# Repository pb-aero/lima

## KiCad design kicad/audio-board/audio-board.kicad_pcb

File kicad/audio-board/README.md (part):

# Audio board (AeroNode side) — clean-slate redo

**Status (measured 2026-11-09):** one A1 sheet, 120 parts (116 + 4 mounting holes), 140 nets, drawn entirely through Konnect.
Netlist matches `doc/design_nets.py` exactly; ERC 0 errors (4 expected strap warnings). All 120 parts have footprints.
The PCB is routed: 0 unconnected pads, 5 parity warnings on text fields only (Datasheet, Cable). **Schematic and layout
are not reviewed, and no board is recorded as built.** Published to the shelf as `reports/peter/LIMA_audio_board.html`.
Sheet notes corrected 2026-11-09, text only: netlist identical before and after. The sheet's title block is still
empty because Konnect has no tool for it; a text note above it identifies the sheet. Set it in Eeschema's Page Settings.
Started 2026-10-22, per Peter:
*"redo the audio board schematic on a clean slate using the new reference diagram from Juliette."*

**Reference:** JULIETT's interface spec, `Aerosense-Dev-Team-Sync:reports/john/2026-10-21_aeronode_audio_flow.pdf`
(company `1cf7160`, 10 pages), with John's 2026-10-21 rulings: the ADAU1467 hub is adopted
(`L-2026-W36-011`), the ADXL354 and ADAU1761 leave production, the cabin mic is single-ended analogue.

**What it replaces:** the ADAU1861 + AD2428 + ADXL354 + LTC6242 + level-shifter board last committed at
`72278d1` (`audio-board.kicad_sch` + `boom-mic-tx-select.kicad_sch`). That board was a different
architecture, not an earlier revision of this one; it stays retrievable from git at that SHA.

## Architecture (from the spec, §1–§2)

- **Normal — entirely digital.** Panel earphone → SP-74 (T2/T3) → high-Z tap → `ADAU1372 ADC1` → ADAU1467
  hub → (a) CM5 for AeroVault, (b) AD2428 → A2B → cups. Pilot voice: cup PDM mic → A2B → hub → CM5
  PureVoice → hub → `ADAU1372 DAC0` → buffer → K1 → panel mic line.
- **Bypass — entirely analogue, entirely aircraft-powered.** Panel audio → SP-74 → cup K2 N.C. → driver.
  Failsafe electret (console-biased) → K1 de-energised → panel mic line.
- **Cabin mic:** IM68A130A, single-ended analogue → `ADAU1372 ADC0`. No I²S mic.
- **Clock:** one 12.288 MHz XO → ADAU1467 `XTALIN/MCLK`; hub distributes `CLKOUT` and BCLK/LRCLK to the
  1372, CM5 (slave) and AD2428. Hub self-boots from EEPROM.
- **ICM-45686** (DVNC reference) is on SPI to the CM5 and never enters the audio chain — not on this board.

## Rulings (Peter, 2026-10-22)

| # | Ruling | Note |
|---|---|---|
| 1 | **Keep A2B**, per the spec | Peter floated I²S + power + bypass over an HDMI-type cable with JST ends, then withdrew it |
| 2 | **K1 = Panasonic AQW612S pair**, same as cup K2 | One package per leg; Form B (LED off) = electret → panel mic = bypass; Form A (LED on) = DAC → panel mic. Both legs broken, so our ground leaves the electret loop. Replaces the spec's "relay" and my earlier G6K-2 suggestion. At mic-level impedances (~1 kΩ) the 2.5 Ω on-resistance is negligible, so K2's open THD question barely applies here `[derived]` |
| 3 | ~~K1 LEDs driven from a TPS3430 watchdog kicked by the PureVoice process~~ | Ruled earlier the same day, then **superseded by 4** once the bare TPS3430 turned out not to latch (below) |
| 4 | **Watchdog left off for now** | K1 LEDs driven from a CM5 GPIO through a transistor, LEDs **off** at GPIO reset/high-Z (pull-down on the base), so power loss and CM5 boot both sit in bypass. `[default]` — the GPIO drive is my choice, not Peter's words. **Accepted residual:** power present + CM5 hung leaves K1 in NORMAL with a silent DAC on the panel mic — the spec §3 failure mode. Leave footprint room for a TPS3430 + 74LVC1G74 so it can return without a re-spin |
| 5 | ~~A2B part is the AD2428, not the AD2433~~ — **superseded by 6 the same day** — both ends (AeroNode main node, each cup sub-node) | Peter, 2026-10-22, after the AD2433's full data sheet turned out to be NDA-only. **Reverses the 2026-09-25 choice** (JULIETT `2026-09-25-003`), whose reason was that the AD2428W has **no SPI**, so DVNC/ANC coefficients cannot go *CM5 → SPI → A2B → cup ADAU1861* as spec §2 draws. They go by **A2B remote I²C** instead. `docs/a2b-remote-i2c-throughput.md` (2026-09-25) found that viable: 14 kB/s against a 384 kB/s control-header ceiling `[derived]`. **Condition carried with it:** erratum 18000075 — a failed remote-I²C write may not report an error, so coefficients must be written with **read-back verification**, or the canceller silently stops tracking; erratum 18000052 — remote I²C contends with GPIO-over-distance for the same header fields. **John/JULIETT not yet told** |
| 6 | ~~A2B part is the AD2433 at both ends~~ — **superseded by 9** — AeroNode main node and each cup sub-node | Peter, 2026-10-22, once the SPI point was clear. Restores JULIETT `2026-09-25-003`: coefficients go *CM5 → SPI0 → hub → AD2433 SPI over distance → cup ADAU1861*, landing straight in DSP memory. Ruling 5's remote-I²C errata no longer apply to the coefficient path. **Brings back the NDA blocker** for the AD2433 symbol (below) |
| 7 | **I²S from the CM5 to the audio board** | Peter, 2026-10-22. CM5 is I²S slave to the hub (spec §4). Over the AeroNode's existing audio header J3/J4 — below |
| 8 | **DVNC/ANC coefficients travel as audio data, not SPI** — CM5 → spare I²S lane → hub → A2B downstream TDM slot → cup ADAU1861 serial port → unpacked by the cup DSP | Peter, 2026-10-22, because the AeroNode audio header carries no SPI (option 1 of the three below). **Lane:** `I2S1_SDO1` (J3.7) `[default]`. **Requirements this creates:** (a) the hub must route that channel **bit-exact** — no gain, mix, ASRC, dither or limiter on it; (b) the stream carries its own **framing + CRC**, and the cup **keeps its previous coefficients** when a block fails — an audio slot has no ACK; (c) **cup firmware** work on the HiFi 3z, the cost JULIETT's SPI route avoided; (d) **one more downstream slot** in the A2B TDM map (still unfrozen). Bandwidth: 1 slot × 32 bit × 48 kHz = 1.536 Mbit/s vs ~112 kbit/s needed `[derived]`. **Consequence:** the AD2433's only stated advantage over the AD2428 was SPI-over-A2B for exactly this path (JULIETT `2026-09-25-003`), so ruling 6's reason no longer holds — the AD2428 (non-NDA, symbol already in the library) would serve. **Ruled in 9.** John/JULIETT not told |
| 9 | **A2B part is the AD2428 at both ends** — AeroNode main node and each cup sub-node | Peter, 2026-10-22, once ruling 8 took SPI out of the coefficient path: full data sheet public (`docs/datasheets/AD242x_RevC.pdf`), symbol already in `AnalogDevices`. Remote I²C over A2B is now **control traffic only**, so errata 18000075/18000052 touch configuration, not the canceller. **Slot capacity `[fetched]`** AD242x TRM: *"Up to 32 channels (1 x TDM32 or 2 x TDM16)"*, TDM2–TDM32 per pin — the two-slot cap asked about in JULIETT `2026-09-25-003` §2.3 is the PDM-clocked-from-BCLK case only (TDM2/32 or TDM4/16), which does not apply: the cup voice mic is on the ADAU1861's DMIC, not the AD2428's PDM pins |
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
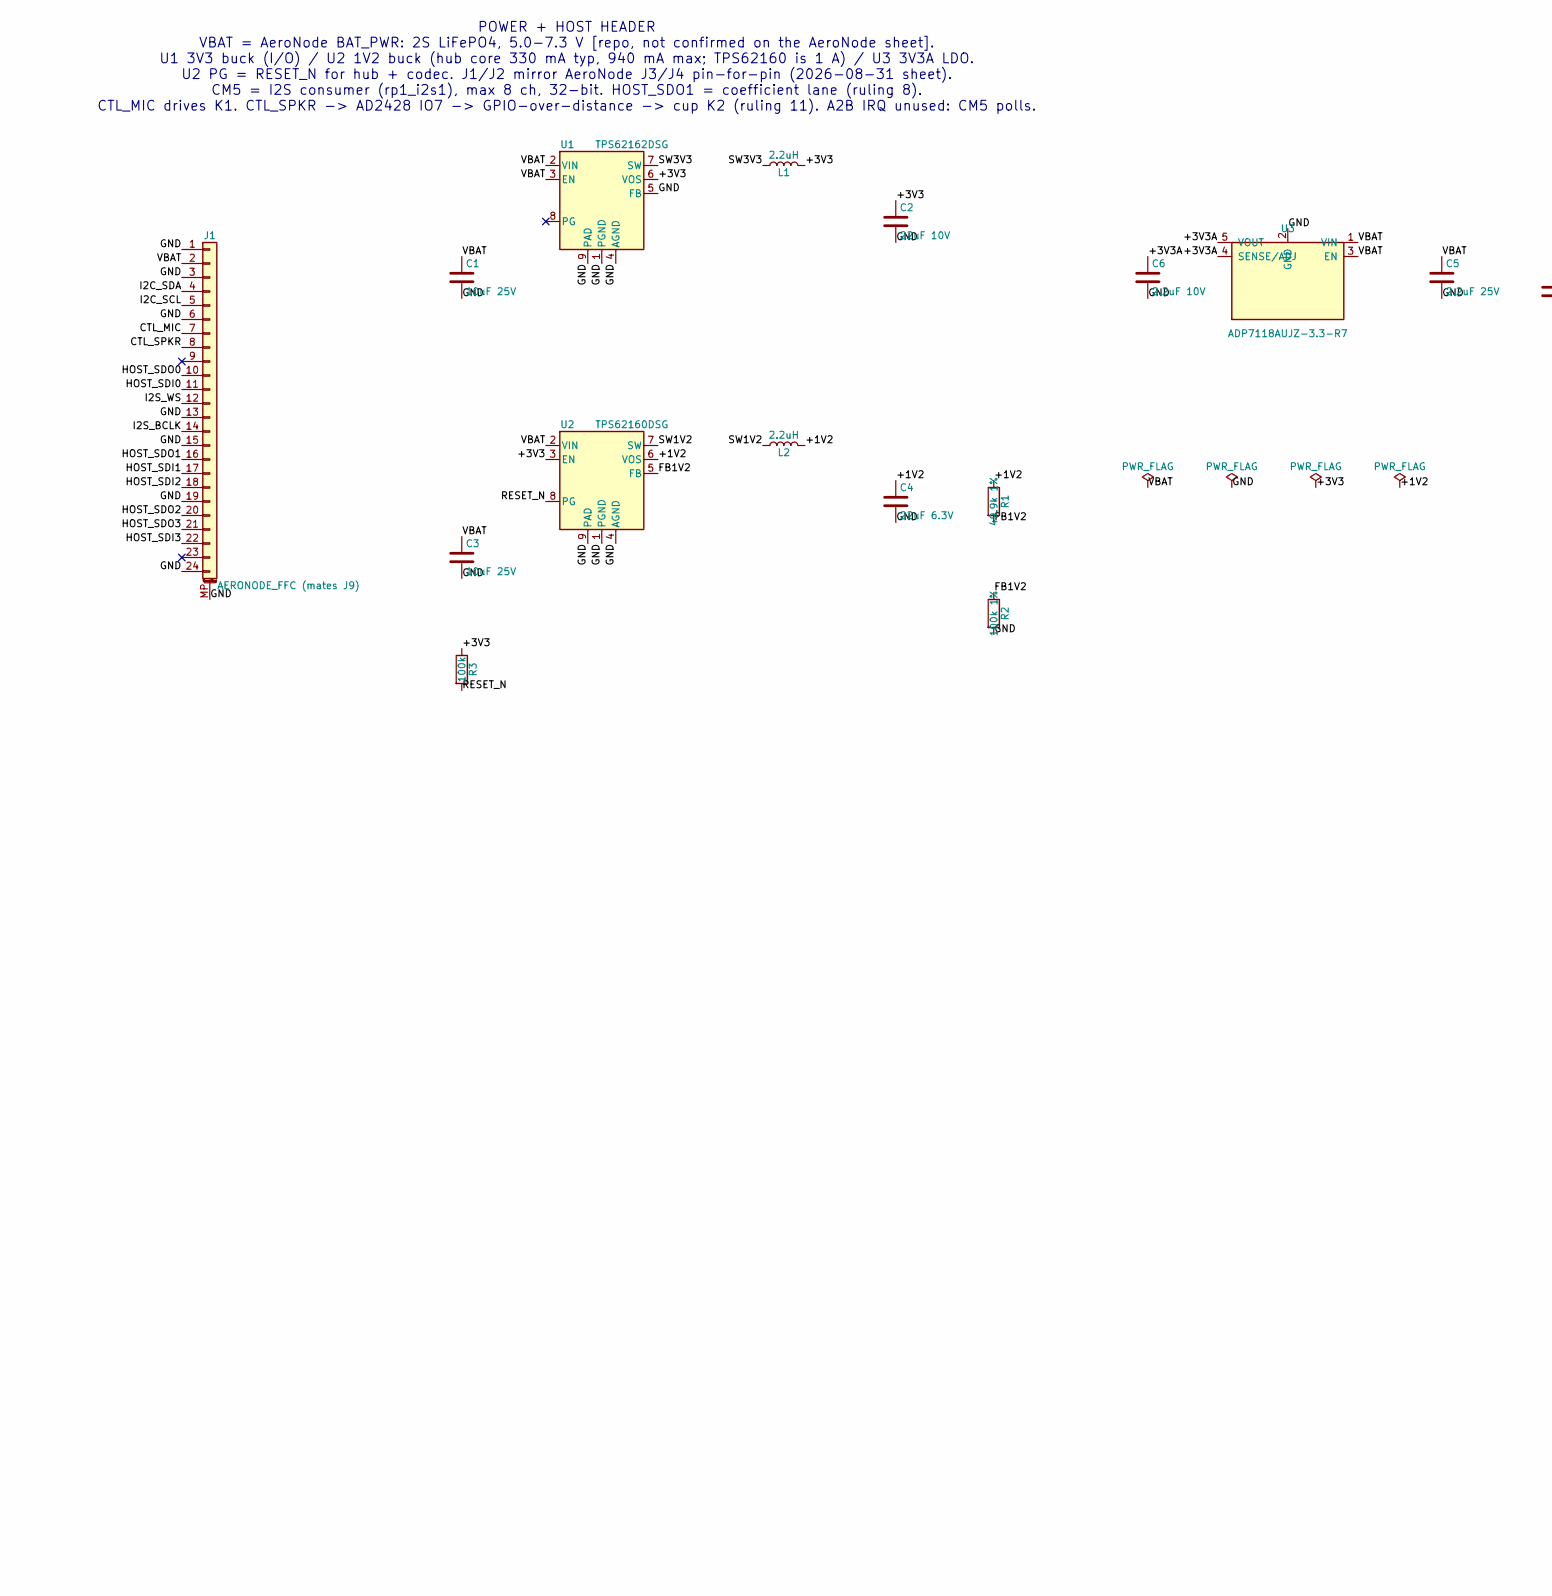
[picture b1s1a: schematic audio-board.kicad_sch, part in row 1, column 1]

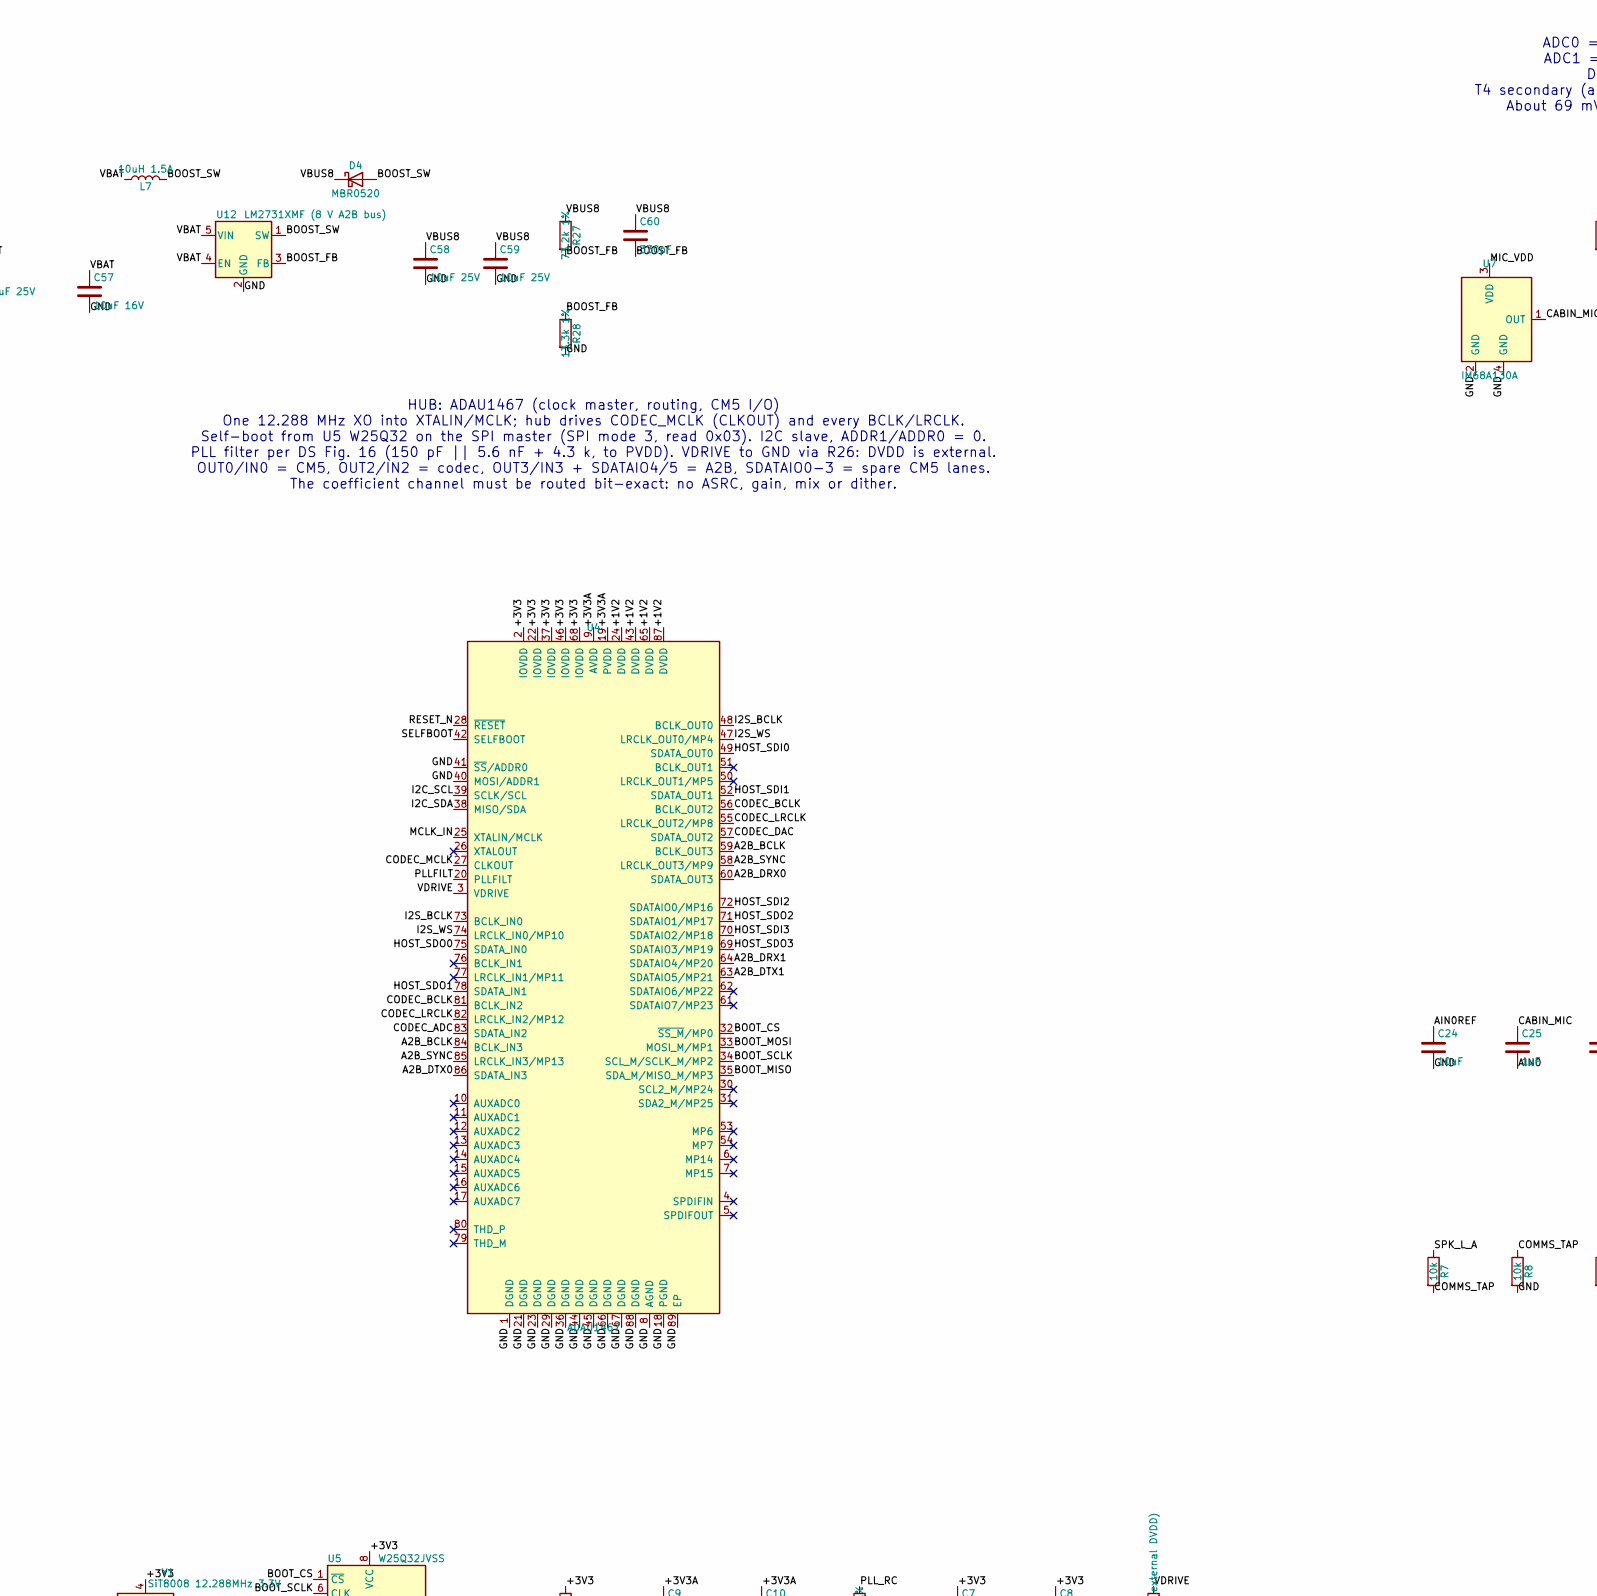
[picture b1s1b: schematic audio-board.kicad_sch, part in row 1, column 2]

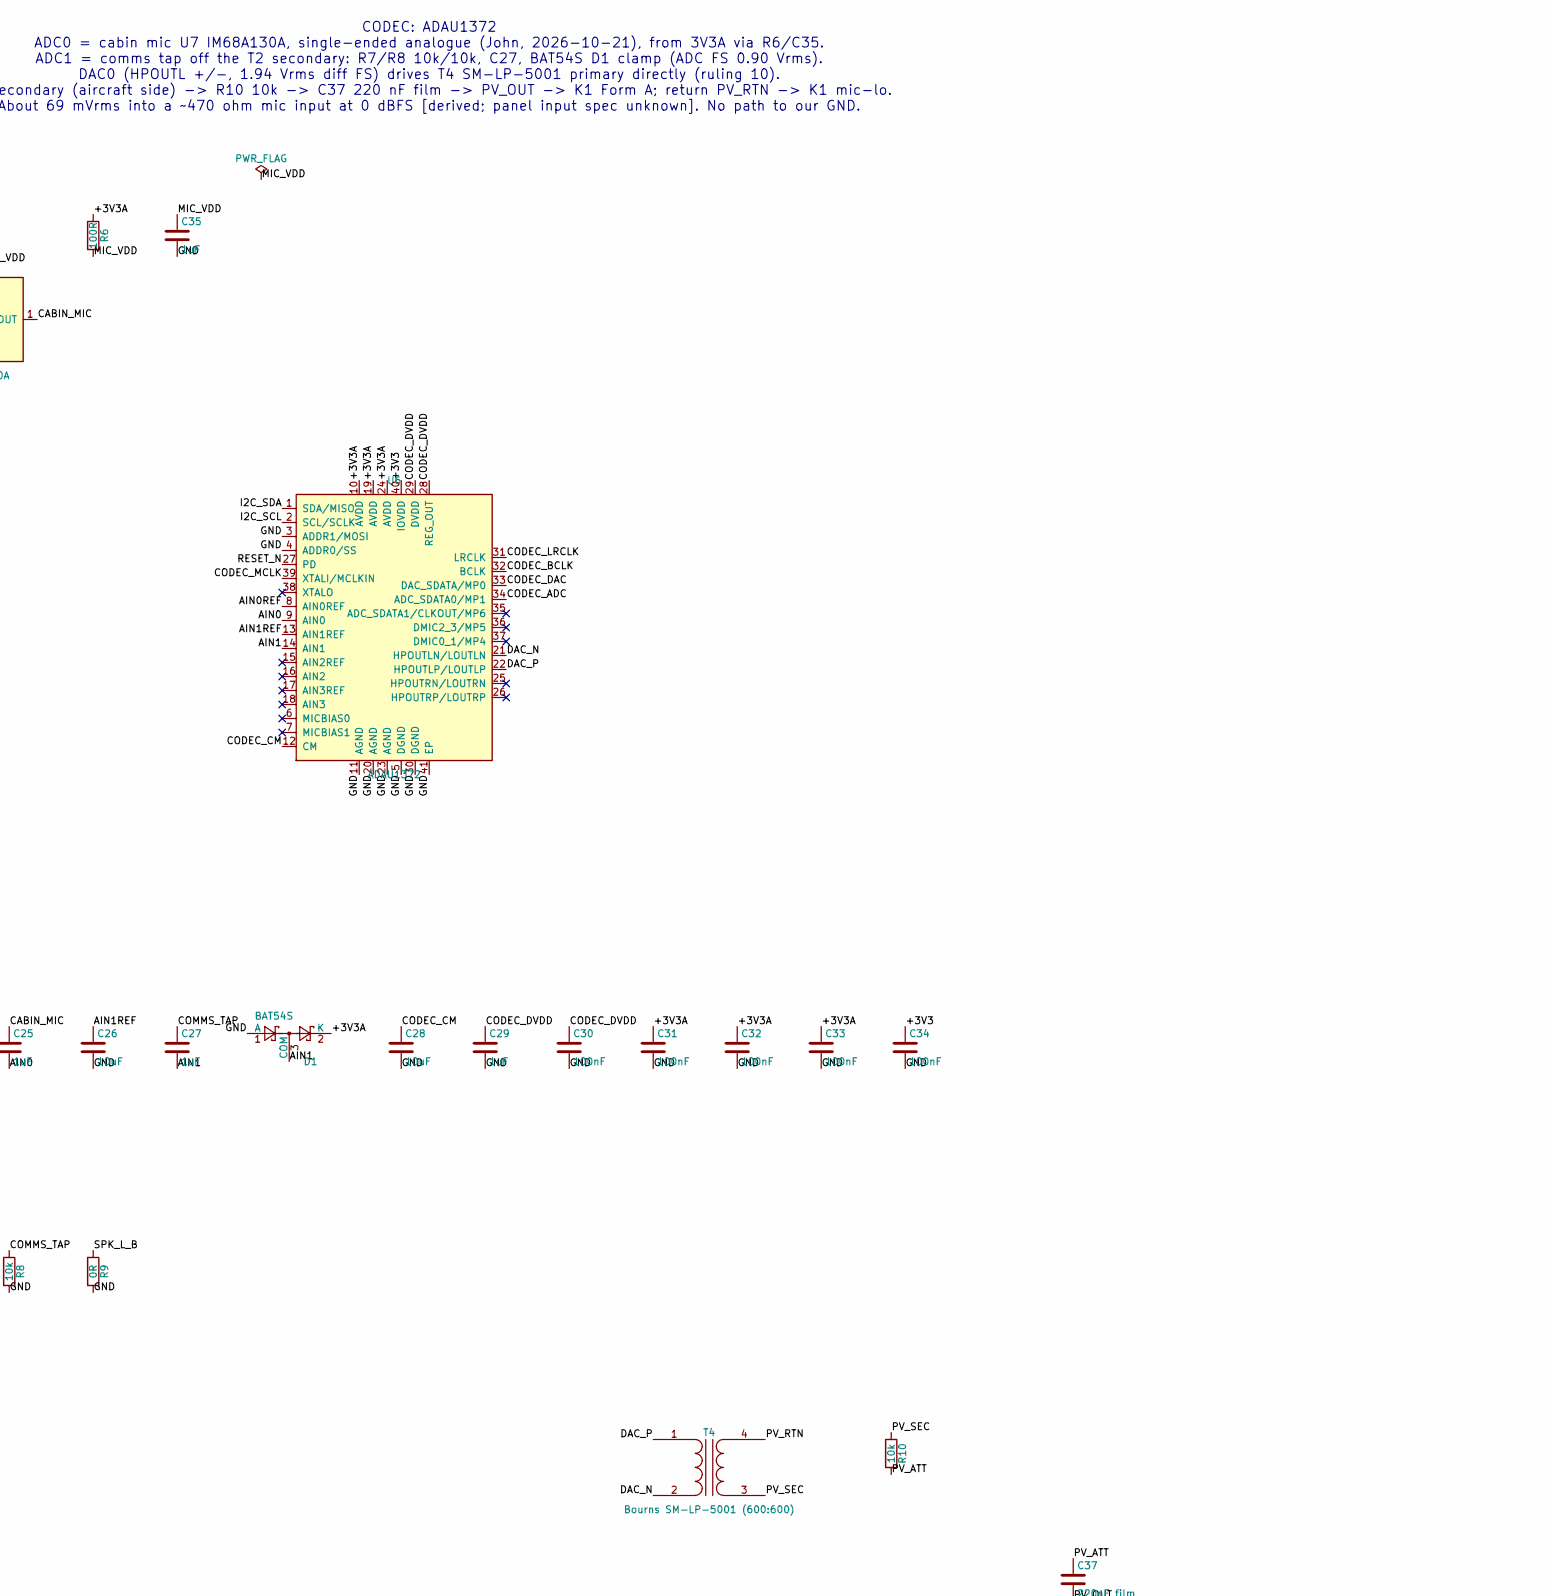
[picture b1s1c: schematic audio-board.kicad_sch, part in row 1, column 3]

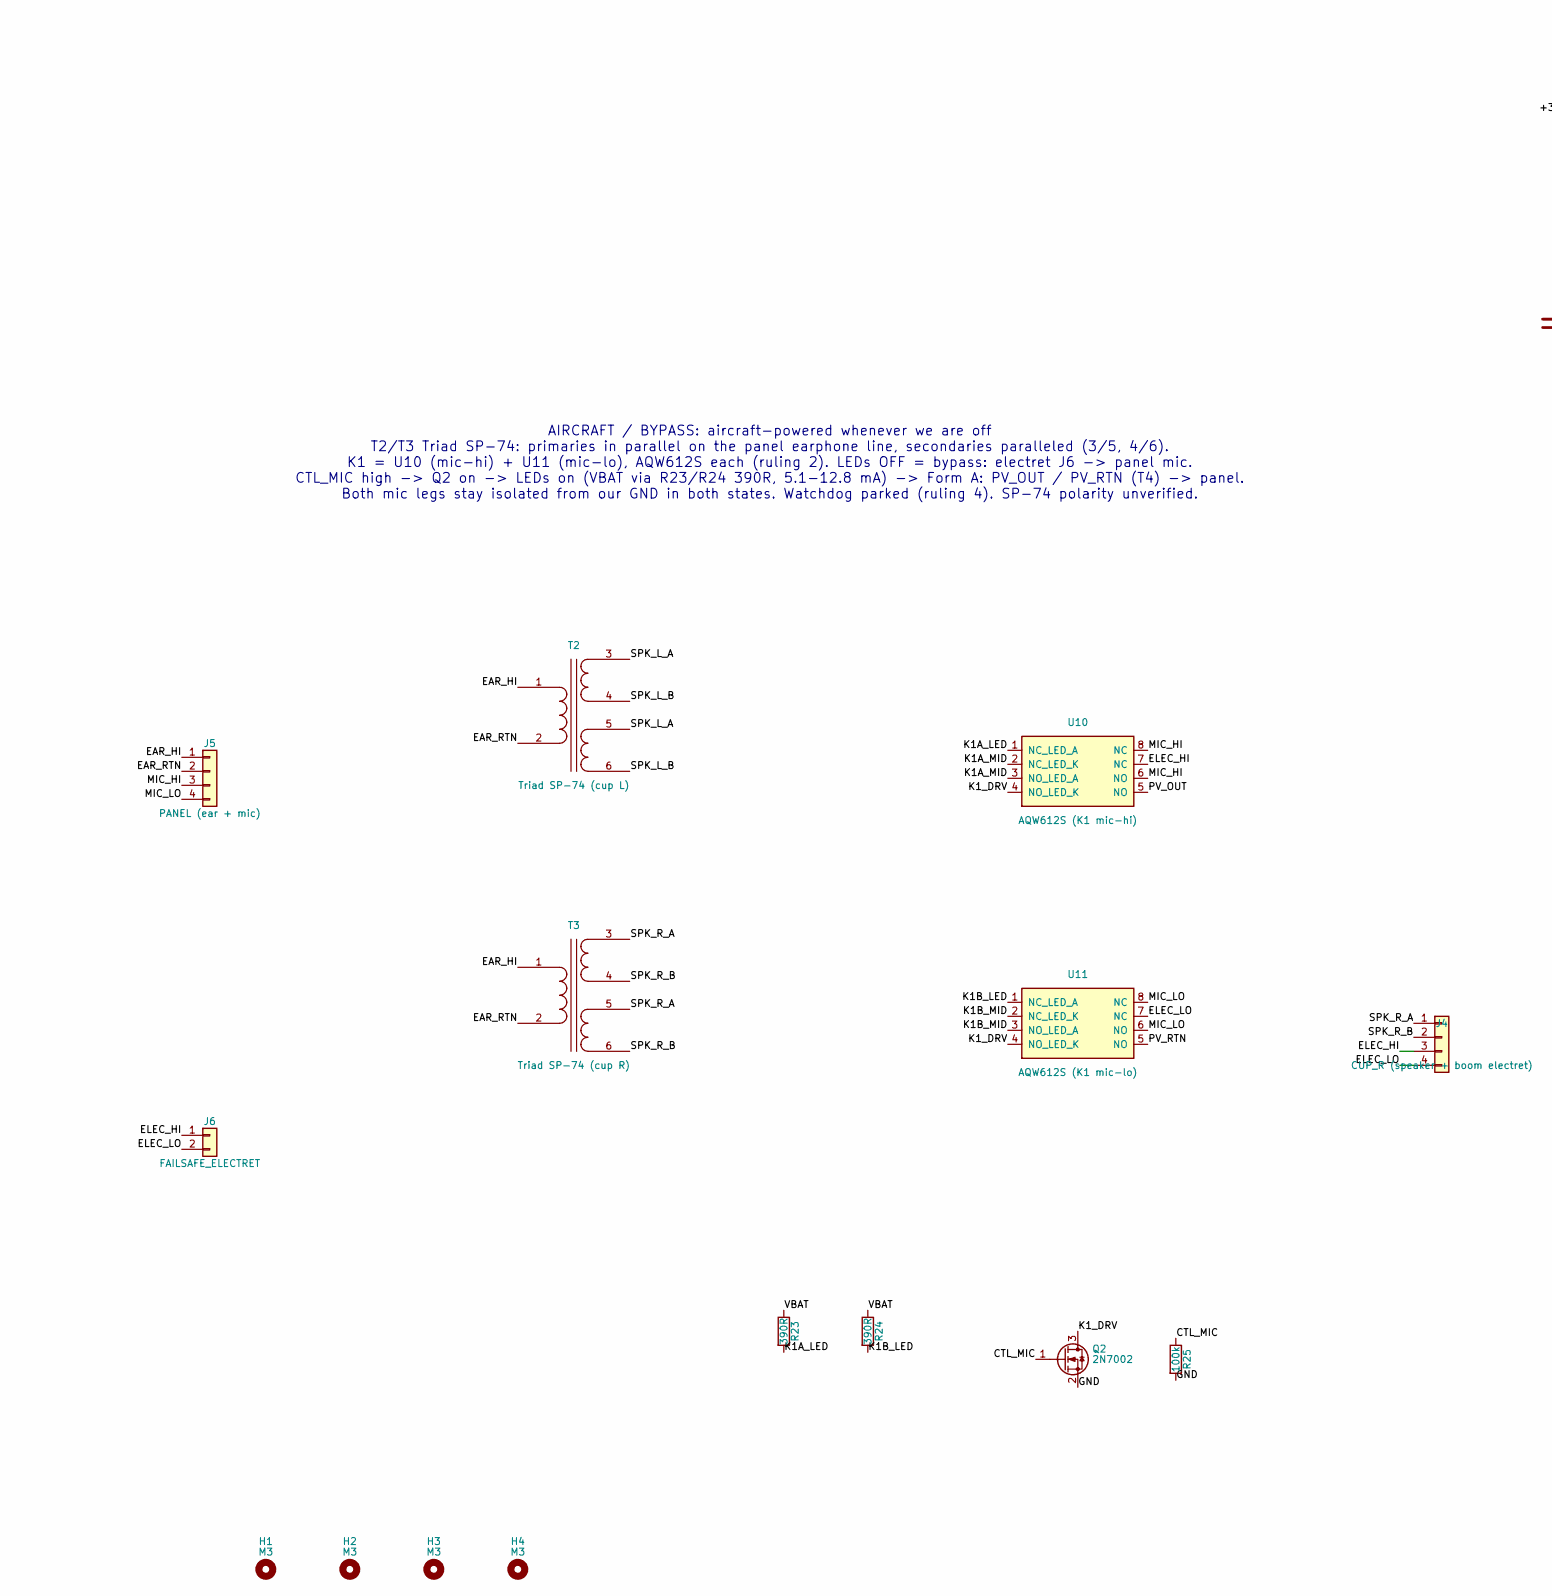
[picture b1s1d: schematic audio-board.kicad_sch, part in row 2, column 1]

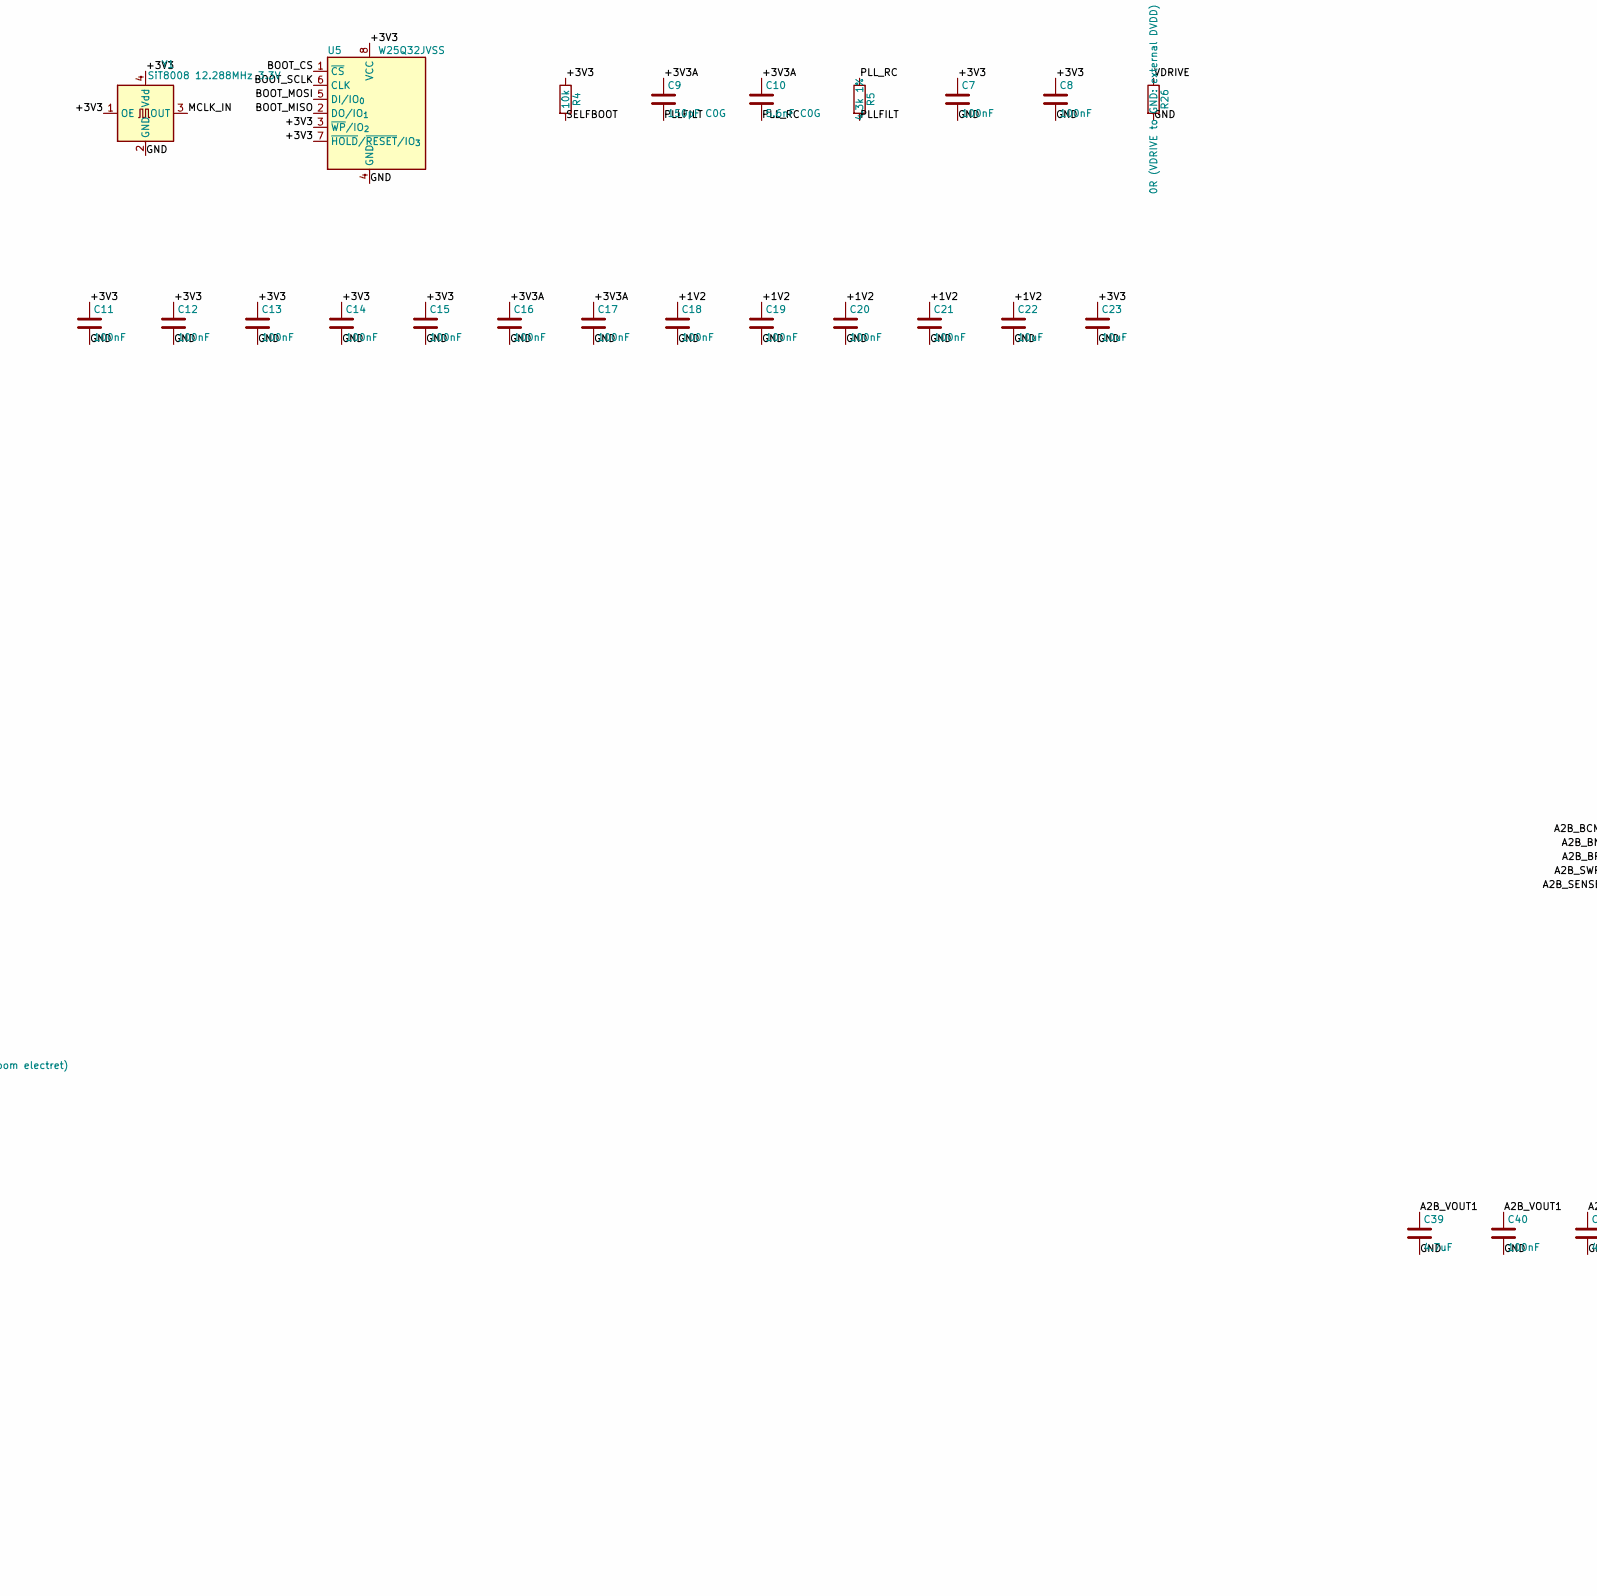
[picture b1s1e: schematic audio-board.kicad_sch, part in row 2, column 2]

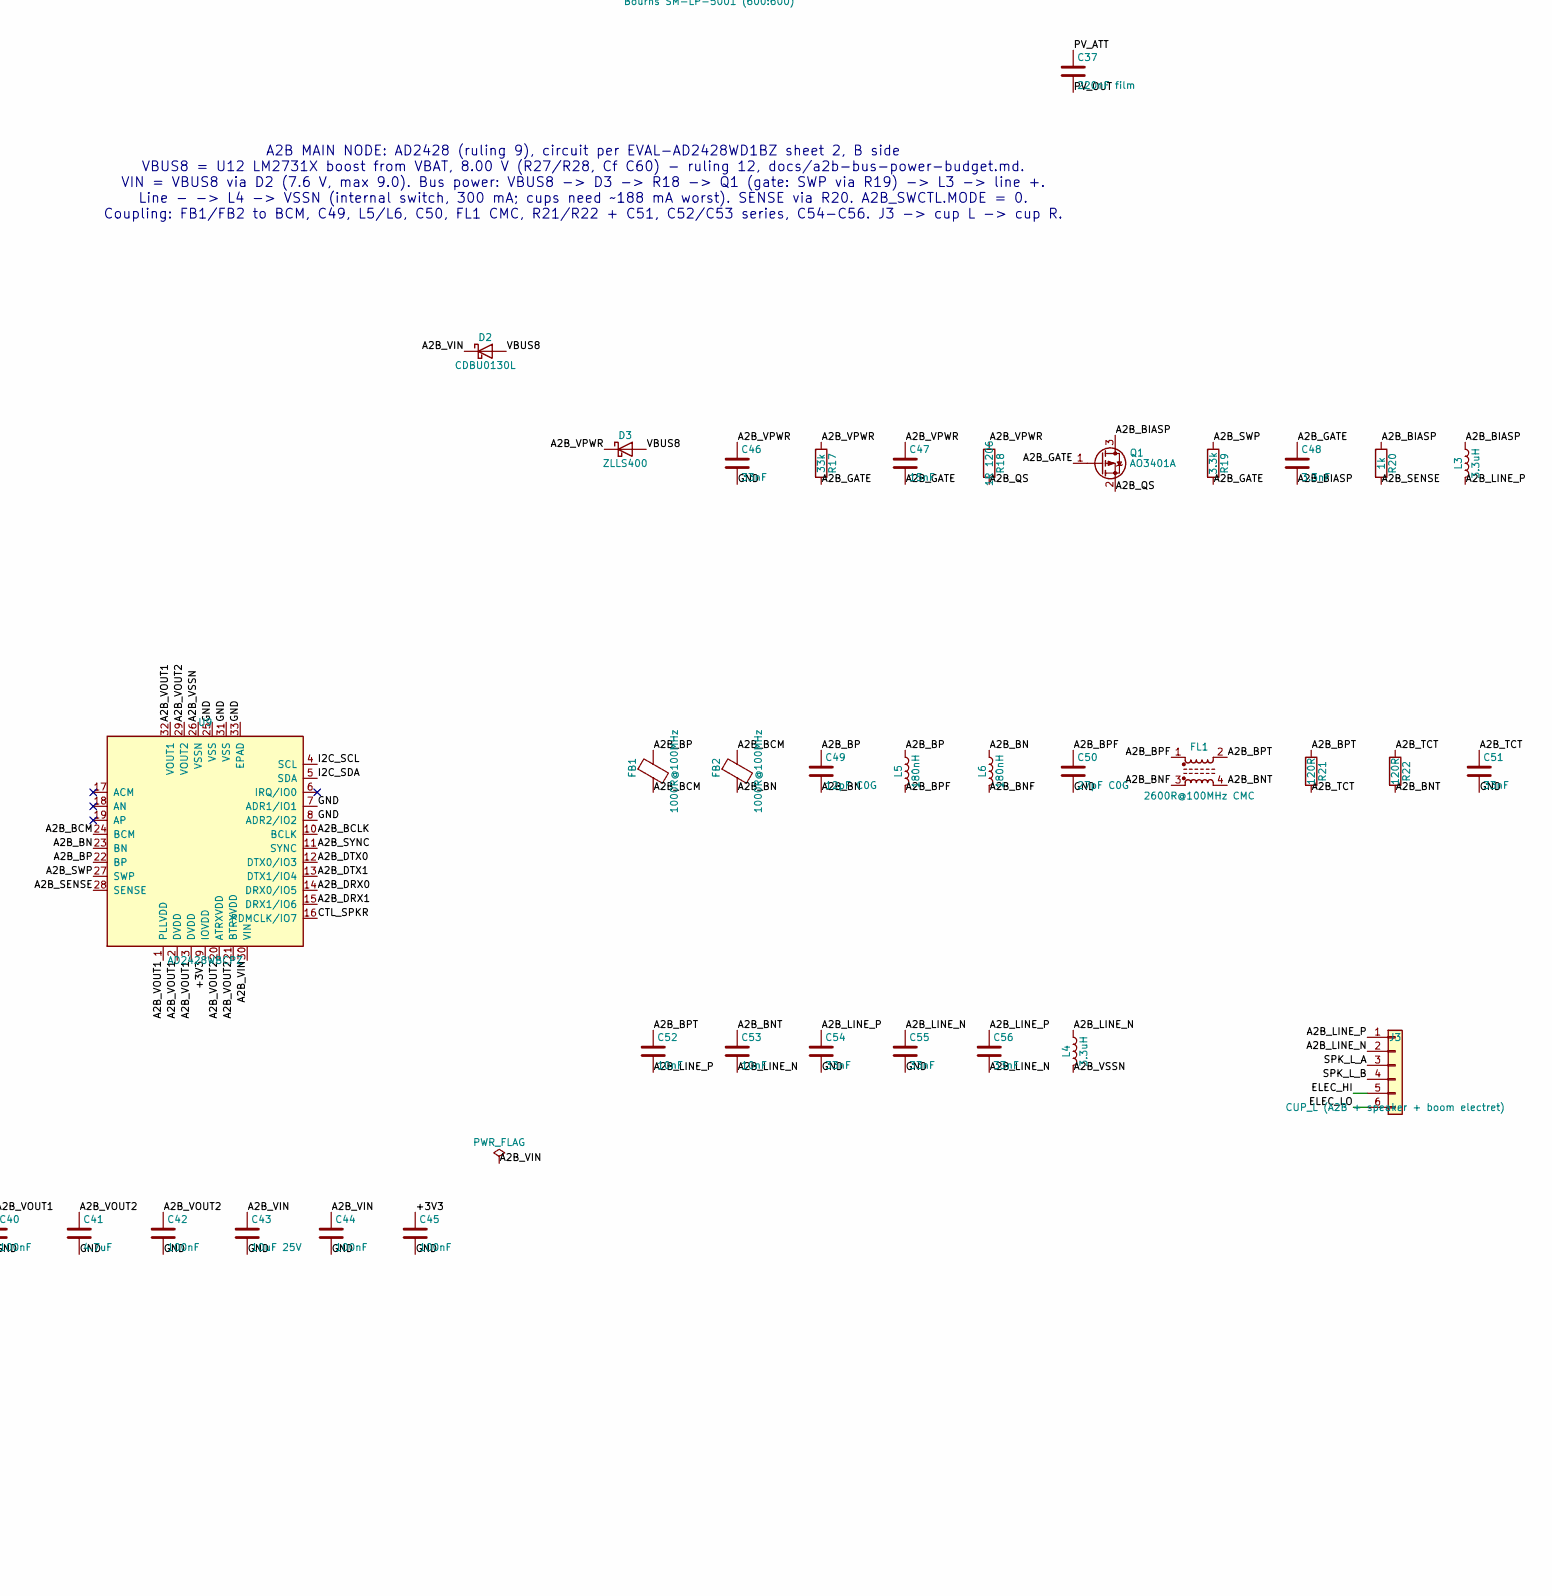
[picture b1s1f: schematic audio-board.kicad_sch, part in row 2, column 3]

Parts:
C1, C3, C43, C58, C59: 10uF 25V; C_0805_2012Metric
C2: 22uF 10V; C_0805_2012Metric
C4: 22uF 6.3V; C_0805_2012Metric
C5: 2.2uF 25V; C_0603_1608Metric
C6: 2.2uF 10V; C_0603_1608Metric
C7, C8, C11, C12, C13, C14, C15, C16, C17, C18, C19, C20, C21, C30, C31, C32, C33, C34, C40, C42, C44, C45: 100nF; C_0603_1608Metric
C9: 150pF C0G; C_0603_1608Metric
C10: 5.6nF C0G; C_0603_1608Metric
C22, C23, C24, C26, C28: 10uF; C_0805_2012Metric
C25, C27, C29, C35: 1uF; C_0603_1608Metric
C37: 220nF film; C_1812_4532Metric
C39, C41: 4.7uF; C_0603_1608Metric
C46, C51, C54, C55, C56: 33nF; C_0603_1608Metric
C47: 15nF; C_0603_1608Metric
C48: 3.3nF; C_0603_1608Metric
C49: 12pF C0G; C_0603_1608Metric
C50: 27pF C0G; C_0603_1608Metric
C52, C53: 10nF; C_0603_1608Metric
C57: 10uF 16V; C_0805_2012Metric
C60: 330pF; C_0603_1608Metric
D1: BAT54S; SOT-23
D2: CDBU0130L; D_0603_1608Metric
D3: ZLLS400; D_SOD-323
D4: MBR0520; D_SOD-123
FB1, FB2: 1000R@100MHz; L_0603_1608Metric
FL1: 2600R@100MHz CMC; L_CommonModeChoke_Coilank_ACM3216
H1, H2, H3, H4: M3; MountingHole_3.2mm_M3
J1: AERONODE_FFC (mates J9); Cvilux_CF31241D0R0-05-NH_1x24-1MP_P0.5mm_Horizontal; MPN Cvilux CF31241D0R0-05-NH
J3: CUP_L (A2B + speaker + boom electret); JST_GH_SM06B-GHS-TB_1x06-1MP_P1.25mm_Horizontal
J4: CUP_R (speaker + boom electret); JST_GH_SM04B-GHS-TB_1x04-1MP_P1.25mm_Horizontal
J5: PANEL (ear + mic); JST_GH_SM04B-GHS-TB_1x04-1MP_P1.25mm_Horizontal
J6: FAILSAFE_ELECTRET; JST_GH_SM02B-GHS-TB_1x02-1MP_P1.25mm_Horizontal
L1, L2: 2.2uH; L_1008_2520Metric
L3, L4: 3.3uH; L_1210_3225Metric
L5, L6: 180nH; L_0603_1608Metric
L7: 10uH 1.5A; L_Coilcraft_XAL4030-XXX
Q1: AO3401A; SOT-23
Q2: 2N7002; SOT-23
R1: 49.9k 1%; R_0603_1608Metric
R2: 100k 1%; R_0603_1608Metric
R3, R25: 100k; R_0603_1608Metric
R4, R7, R8, R10: 10k; R_0603_1608Metric
R5: 4.3k 1%; R_0603_1608Metric
R6: 100R; R_0603_1608Metric
R9: 0R; R_0603_1608Metric
R17: 33k; R_0603_1608Metric
R18: 1R 1206; R_1206_3216Metric
R19: 3.3k; R_0603_1608Metric
R20: 1k; R_0603_1608Metric
R21, R22: 120R; R_0603_1608Metric
R23, R24: 390R; R_0603_1608Metric
R26: 0R (VDRIVE to GND: external DVDD); R_0603_1608Metric
R27: 73.2k 1%; R_0603_1608Metric
R28: 13.3k 1%; R_0603_1608Metric
T2: Triad SP-74 (cup L); Triad_SP-74_THT_10.4x7.9mm_P2.54mm
T3: Triad SP-74 (cup R); Triad_SP-74_THT_10.4x7.9mm_P2.54mm
T4: Bourns SM-LP-5001 (600:600); Bourns_SM-LP-5001_12.8x9.0mm_P2.54mm
U1: TPS62162DSG; WSON-8-1EP_2x2mm_P0.5mm_EP0.9x1.6mm_ThermalVias
U2: TPS62160DSG; WSON-8-1EP_2x2mm_P0.5mm_EP0.9x1.6mm_ThermalVias
U3: ADP7118AUJZ-3.3-R7; TSOT-23-5
U4: ADAU1467; AD_LFCSP-88-1EP_12x12mm_P0.5mm_EP5.3x5.3mm_CP-88-10
U5: W25Q32JVSS; SOIC-8_5.3x5.3mm_P1.27mm
U6: ADAU1372; AD_LFCSP-40-1EP_6x6mm_P0.5mm_EP4.3x4.3mm_CP-40-10
U7: IM68A130A; Infineon_PG-TLGA-4-2_3.35x2.5mm_IM68A130A
U9: AD2428WBCPZ; QFN-32-1EP_5x5mm_P0.5mm_EP3.6x3.6mm_ThermalVias
U10: AQW612S (K1 mic-hi); Panasonic_GU-SOP8_4.4x9.37mm_P2.54mm_AQW61xS
U11: AQW612S (K1 mic-lo); Panasonic_GU-SOP8_4.4x9.37mm_P2.54mm_AQW61xS
U12: LM2731XMF (8 V A2B bus); SOT-23-5
Y1: SiT8008 12.288MHz 3.3V; Oscillator_SMD_SiT_PQFN-4Pin_3.2x2.5mm

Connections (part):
/+1V2: C4.1, C18.1, C19.1, C20.1, C21.1, C22.1, L2.2, R1.1, U2.6 (VOS), U4.24 (DVDD), U4.43 (DVDD), U4.65 (DVDD), U4.87 (DVDD)
/+3V3: C2.1, C7.1, C8.1, C11.1, C12.1, C13.1, C14.1, C15.1, C23.1, C34.1, C45.1, L1.2, R3.1, R4.1, U1.6 (VOS), U2.3 (EN), U4.2 (IOVDD), U4.22 (IOVDD), U4.37 (IOVDD), U4.46 (IOVDD), U4.68 (IOVDD), U5.3 (~WP/IO_{2}), U5.7 (~HOLD/~RESET/IO_{3}), U5.8 (VCC), U6.40 (IOVDD), U9.9 (IOVDD), Y1.1 (OE), Y1.4 (Vdd)
/+3V3A: C6.1, C9.1, C10.1, C16.1, C17.1, C31.1, C32.1, C33.1, D1.2 (K), R6.1, U3.4 (SENSE/ADJ), U3.5 (VOUT), U4.9 (AVDD), U4.19 (PVDD), U6.10 (AVDD), U6.19 (AVDD), U6.24 (AVDD)
/A2B_BCLK: U4.59 (BCLK_OUT3), U4.84 (BCLK_IN3), U9.10 (BCLK)
/A2B_BCM: FB1.2, FB2.1, U9.24 (BCM)
/A2B_BIASP: C48.2, L3.1, Q1.3 (D), R20.1
/A2B_BN: C49.2, FB2.2, L6.1, U9.23 (BN)
/A2B_BNF: FL1.3, L6.2
/A2B_BNT: C53.1, FL1.4, R22.2
/A2B_BP: C49.1, FB1.1, L5.1, U9.22 (BP)
/A2B_BPF: C50.1, FL1.1, L5.2
/A2B_BPT: C52.1, FL1.2, R21.1
/A2B_DRX0: U4.60 (SDATA_OUT3), U9.14 (DRX0/IO5)
/A2B_DRX1: U4.64 (SDATAIO4/MP20), U9.15 (DRX1/IO6)
/A2B_DTX0: U4.86 (SDATA_IN3), U9.12 (DTX0/IO3)
/A2B_DTX1: U4.63 (SDATAIO5/MP21), U9.13 (DTX1/IO4)
/A2B_GATE: C47.2, C48.1, Q1.1 (G), R17.2, R19.2
/A2B_LINE_N: C53.2, C55.1, C56.2, J3.2, L4.1
/A2B_LINE_P: C52.2, C54.1, C56.1, J3.1, L3.2
/A2B_QS: Q1.2 (S), R18.2
/A2B_SENSE: R20.2, U9.28 (SENSE)
/A2B_SWP: R19.1, U9.27 (SWP)
/A2B_SYNC: U4.58 (LRCLK_OUT3/MP9), U4.85 (LRCLK_IN3/MP13), U9.11 (SYNC)
/A2B_TCT: C51.1, R21.2, R22.1
/A2B_VIN: C43.1, C44.1, D2.1 (K), U9.30 (VIN)
/A2B_VOUT1: C39.1, C40.1, U9.1 (PLLVDD), U9.2 (DVDD), U9.3 (DVDD), U9.32 (VOUT1)
/A2B_VOUT2: C41.1, C42.1, U9.20 (ATRXVDD), U9.21 (BTRXVDD), U9.29 (VOUT2)
/A2B_VPWR: C46.1, C47.1, D3.1 (K), R17.1, R18.1
/A2B_VSSN: L4.2, U9.26 (VSSN)
/AIN0: C25.2, U6.9 (AIN0)
/AIN0REF: C24.1, U6.8 (AIN0REF)
/AIN1: C27.2, D1.3 (COM), U6.14 (AIN1)
/AIN1REF: C26.1, U6.13 (AIN1REF)
/BOOST_FB: C60.2, R27.2, R28.1, U12.3 (FB)
/BOOST_SW: D4.2 (A), L7.2, U12.1 (SW)
/BOOT_CS: U4.32 (~SS_M/MP0), U5.1 (~CS)
/BOOT_MISO: U4.35 (SDA_M/MISO_M/MP3), U5.2 (DO/IO_{1})
/BOOT_MOSI: U4.33 (MOSI_M/MP1), U5.5 (DI/IO_{0})
/BOOT_SCLK: U4.34 (SCL_M/SCLK_M/MP2), U5.6 (CLK)
/CABIN_MIC: C25.1, U7.1 (OUT)
/CODEC_ADC: U4.83 (SDATA_IN2), U6.34 (ADC_SDATA0/MP1)
/CODEC_BCLK: U4.56 (BCLK_OUT2), U4.81 (BCLK_IN2), U6.32 (BCLK)
/CODEC_CM: C28.1, U6.12 (CM)
/CODEC_DAC: U4.57 (SDATA_OUT2), U6.33 (DAC_SDATA/MP0)
/CODEC_DVDD: C29.1, C30.1, U6.28 (REG_OUT), U6.29 (DVDD)
/CODEC_LRCLK: U4.55 (LRCLK_OUT2/MP8), U4.82 (LRCLK_IN2/MP12), U6.31 (LRCLK)
/CODEC_MCLK: U4.27 (CLKOUT), U6.39 (XTALI/MCLKIN)
/COMMS_TAP: C27.1, R7.2, R8.1
/CTL_MIC: J1.7, Q2.1 (G), R25.1
/CTL_SPKR: J1.8, U9.16 (PDMCLK/IO7)
/DAC_N: T4.2 (AB), U6.21 (HPOUTLN/LOUTLN)
/DAC_P: T4.1 (AA), U6.22 (HPOUTLP/LOUTLP)
/EAR_HI: J5.1, T2.1 (AA), T3.1 (AA)
/EAR_RTN: J5.2, T2.2 (AB), T3.2 (AB)
/ELEC_HI: J3.5, J4.3, J6.1, U10.7 (NC)
/ELEC_LO: J3.6, J4.4, J6.2, U11.7 (NC)
/FB1V2: R1.2, R2.1, U2.5 (FB)
/GND: C1.2, C2.2, C3.2, C4.2, C5.2, C6.2, C7.2, C8.2, C11.2, C12.2, C13.2, C14.2, C15.2, C16.2, C17.2, C18.2, C19.2, C20.2, C21.2, C22.2, C23.2, C24.2, C26.2, C28.2, C29.2, C30.2, C31.2, C32.2, C33.2, C34.2, C35.2, C39.2, C40.2, C41.2, C42.2, C43.2, C44.2, C45.2, C46.2, C50.2, C51.2, C54.2, C55.2, C57.2, C58.2, C59.2, D1.1 (A), J1.1, J1.3, J1.6, J1.13, J1.15, J1.19, J1.24, J1.MP (MountPin), Q2.2 (S), R2.2, R8.2, R9.2, R25.2, R26.2, R28.2, U1.1 (PGND), U1.4 (AGND), U1.5 (FB), U1.9 (PAD), U2.1 (PGND), U2.4 (AGND), U2.9 (PAD), U3.2 (GND), U4.1 (DGND), U4.8 (AGND), U4.18 (PGND), U4.21 (DGND), U4.23 (DGND), U4.29 (DGND), U4.36 (DGND), U4.40 (MOSI/ADDR1), U4.41 (~SS/ADDR0), U4.44 (DGND)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
/HOST_SDI0: J1.11, U4.49 (SDATA_OUT0)
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
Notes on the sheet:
HUB: ADAU1467 (clock master, routing, CM5 I/O) One 12.288 MHz XO into XTALIN/MCLK; hub drives CODEC_MCLK (CLKOUT) and every BCLK/LRCLK. Self-boot from U5 W25Q32 on the SPI master (SPI mode 3, read 0x03). I2C slave, ADDR1/ADDR0 = 0. PLL filter per DS Fig. 16 (150 pF || 5.6 nF + 4.3 k, to PVDD). VDRI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
CODEC: ADAU1372 ADC0 = cabin mic U7 IM68A130A, single-ended analogue (John, 2026-10-21), from 3V3A via R6/C35. ADC1 = comms tap off the T2 secondary: R7/R8 10k/10k, C27, BAT54S D1 clamp (ADC FS 0.90 Vrms). DAC0 (HPOUTL +/-, 1.94 Vrms diff FS) drives T4 SM-LP-5001 primary directly (ruling 10). T4 se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
AIRCRAFT / BYPASS: aircraft-powered whenever we are off T2/T3 Triad SP-74: primaries in parallel on the panel earphone line, secondaries paralleled (3/5, 4/6). K1 = U10 (mic-hi) + U11 (mic-lo), AQW612S each (ruling 2). LEDs OFF = bypass: electret J6 -> panel mic. CTL_MIC high -> Q2 on -> LEDs on (V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
POWER + HOST HEADER VBAT = AeroNode BAT_PWR: 2S LiFePO4, 5.0-7.3 V [repo, not confirmed on the AeroNode sheet]. U1 3V3 buck (I/O) / U2 1V2 buck (hub core 330 mA typ, 940 mA max; TPS62160 is 1 A) / U3 3V3A LDO. U2 PG = RESET_N for hub + codec. J1/J2 mirror AeroNode J3/J4 pin-for-pin (2026-08-31 shee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
A2B MAIN NODE: AD2428 (ruling 9), circuit per EVAL-AD2428WD1BZ sheet 2, B side VBUS8 = U12 LM2731X boost from VBAT, 8.00 V (R27/R28, Cf C60) - ruling 12, docs/a2b-bus-power-budget.md. VIN = VBUS8 via D2 (7.6 V, max 9.0). Bus power: VBUS8 -> D3 -> R18 -> Q1 (gate: SWP via R19) -> L3 -> line +. Line 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

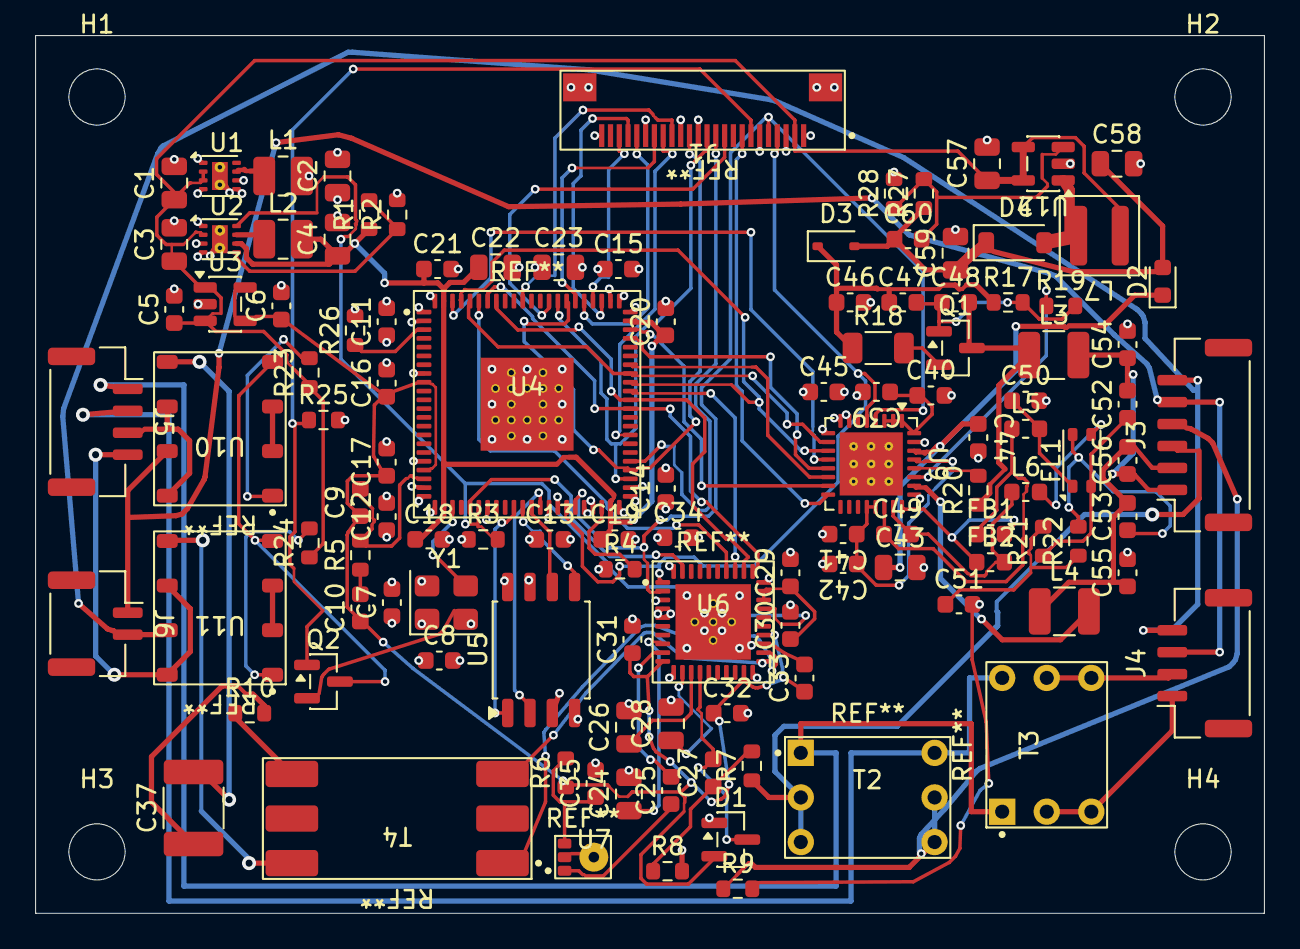
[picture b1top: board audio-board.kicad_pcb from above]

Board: 4 copper layers, 70.0 x 50.0 mm, 120 parts (0 on the bottom side), 96 nets.
